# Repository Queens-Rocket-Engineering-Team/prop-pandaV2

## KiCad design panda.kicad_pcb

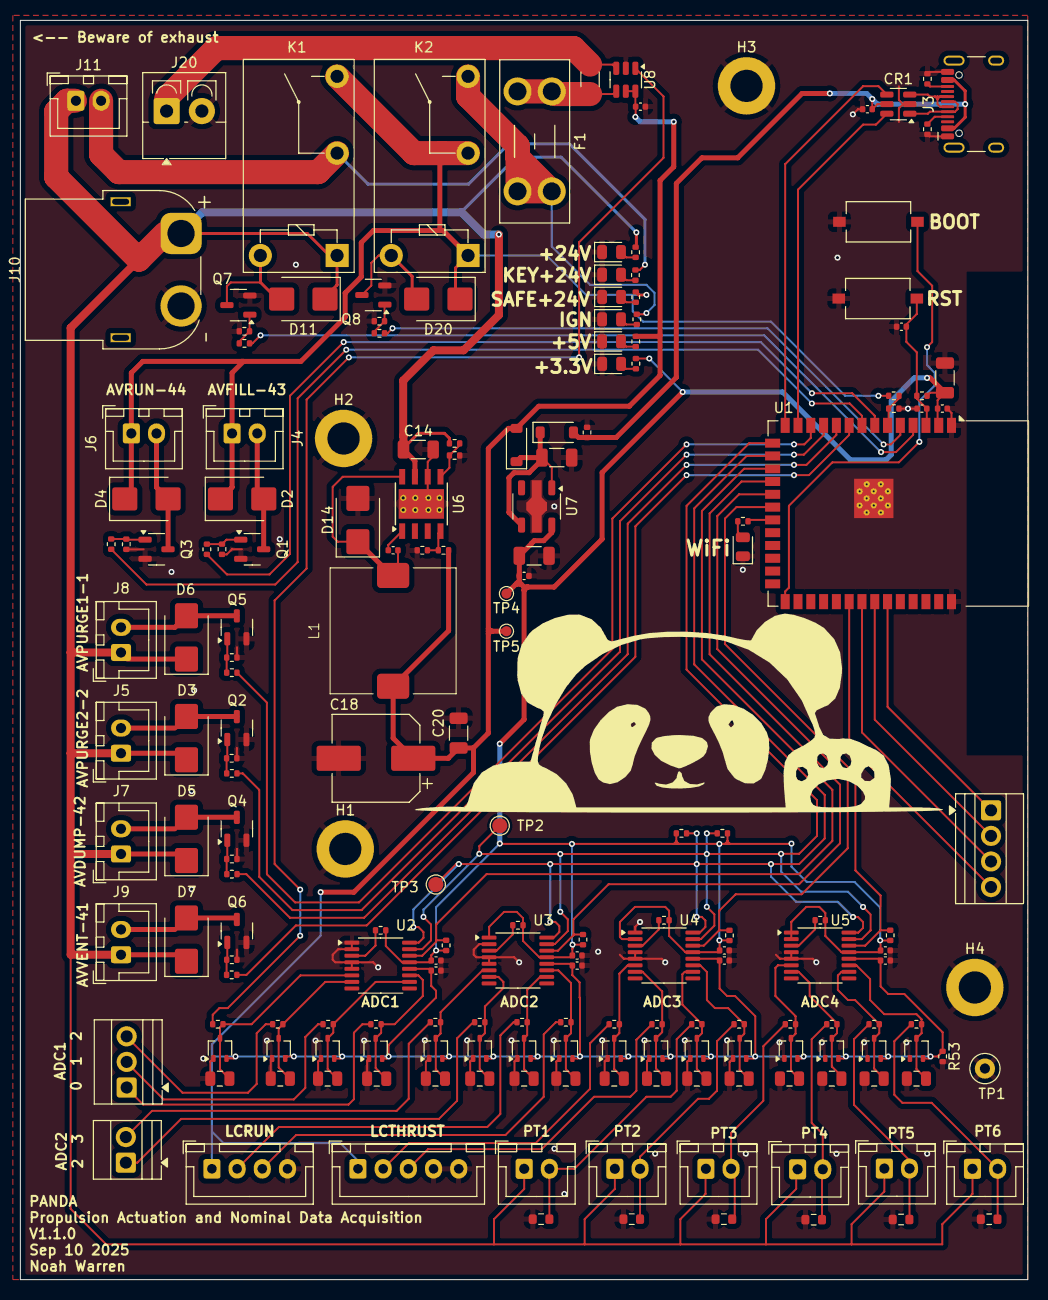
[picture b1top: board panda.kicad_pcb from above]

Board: 2 copper layers, 100.0 x 125.0 mm, 191 parts (0 on the bottom side), 102 nets.

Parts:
C1: 22uF; C_1206_3216Metric
C2, C3, C6, C7, C8, C9, C10, C11, C12, C13, C19, C21: 0.1μF; C_0402_1005Metric
C4: 1μF; C_0402_1005Metric
C5: 0.1uF; C_0402_1005Metric
C14, C15, C17, C20: 10uF; C_1206_3216Metric
C16: 10nF; C_0402_1005Metric
C18: 220uF; CP_Elec_8x10.5
C24, C25, C26, C27, C28, C29, C30, C31, C32, C33, C34, C35, C36, C37, C38, C39: 68nF; C_0805_2012Metric
CR1: USBLC6-2SC6; SOT-23-6
D1: LED-Y; LED_0805_2012Metric
D2, D3, D4, D5, D6, D7, D11, D14, D20: SK44BL; D_SMB
D8, D9, D10, D15, D16, D19: LED-G; LED_0805_2012Metric
D12, D13: 1N5819HW-7-F; D_SOD-123
D21, D22, D23, D24, D25, D26, D27, D28, D29, D30, D31, D32, D33, D34, D35, D36: BAT54SW; SOT-323_SC-70
F1: Fuse; Fuseholder_Blade_Mini_Keystone_3568
H1, H2, H3, H4: MountingHole_Pad; MountingHole_3.2mm_M3_ISO7380_Pad
J1: PIN10-13_Breakout; TerminalBlock_Xinya_XY308-2.54-4P_1x04_P2.54mm_Horizontal
J3: USB_C_Receptacle_USB2.0_16P; USB_C_Receptacle_HCTL_HC-TYPE-C-16P-01A
J4: Valve_1_PWR; JST_XH_B2B-XH-A_1x02_P2.50mm_Vertical
J5: Valve_4_PWR; JST_XH_B2B-XH-A_1x02_P2.50mm_Vertical
J6: Valve_2_PWR; JST_XH_B2B-XH-A_1x02_P2.50mm_Vertical
J7: Valve_5_PWR; JST_XH_B2B-XH-A_1x02_P2.50mm_Vertical
J8: Valve_3_PWR; JST_XH_B2B-XH-A_1x02_P2.50mm_Vertical
J9: Valve_6_PWR; JST_XH_B2B-XH-A_1x02_P2.50mm_Vertical
J10: XT60-M; AMASS_XT60PW-F_1x02_P7.20mm_Horizontal
J11: 24V_Lockout_Key_Switch; JST_XH_B2B-XH-A_1x02_P2.50mm_Vertical
J12: PT_1; JST_XH_B2B-XH-A_1x02_P2.50mm_Vertical
J13: PT_4; JST_XH_B2B-XH-A_1x02_P2.50mm_Vertical
J14: PT_2; JST_XH_B2B-XH-A_1x02_P2.50mm_Vertical
J15: PT_5; JST_XH_B2B-XH-A_1x02_P2.50mm_Vertical
J16: PT_3; JST_XH_B2B-XH-A_1x02_P2.50mm_Vertical
J17: PT_6; JST_XH_B2B-XH-A_1x02_P2.50mm_Vertical
J18: 4-Pin Load Cell; JST_XH_B4B-XH-A_1x04_P2.50mm_Vertical
J19: 5-Pin Load Cell; JST_XH_B5B-XH-A_1x05_P2.50mm_Vertical
J20: Ignitor Screw Terminal; TerminalBlock_4Ucon_1x02_P3.50mm_Vertical
J21: Screw_Terminal_01x03; TerminalBlock_Xinya_XY308-2.54-3P_1x03_P2.54mm_Horizontal
J22: Screw_Terminal_01x02; TerminalBlock_Xinya_XY308-2.54-2P_1x02_P2.54mm_Horizontal
K1, K2: G5Q-1A DC24; Relay_SPST_Omron-G5Q-1A
L1: 22uH 4A; L_12.5x12.5mm_SXNSMDRS1275
Q1, Q2, Q3, Q4, Q5, Q6, Q7, Q8: BSS138; SOT-23-3
R1, R21, R22, R25, R26, R31, R34, R38, R51, R53: 10k; R_0402_1005Metric
R2, R3, R6, R40: 1k; R_0402_1005Metric
R4, R5: 5.1k; R_0402_1005Metric
R7: 270k; R_0402_1005Metric
R8: 33k; R_0402_1005Metric
R9, R10, R13, R14, R17, R18, R35, R52: 100; R_0402_1005Metric
R11, R12, R15, R16, R19, R20, R30, R36: 100k; R_0402_1005Metric
R23, R24, R27, R28, R39: 3.3k; R_0402_1005Metric
R29, R32, R33, R50: 22k; R_0402_1005Metric
R37: 680; R_0402_1005Metric
R41, R42, R43, R44, R45, R46: 250R; R_0603_1608Metric
R49: 25m 1W; R_1206_3216Metric
R54, R55, R56, R57, R58, R59, R60, R61, R62, R63, R64, R65, R66, R67, R68, R69: 2.2k; R_0402_1005Metric
SW1, SW2: PTS636SM43SMTR LFS; SW_Tactile_SPST_NO_Straight_CK_PTS636Sx25SMTRLFS
TP1: TestPoint; TestPoint_Loop_D2.50mm_Drill1.0mm
TP2: SDA; TestPoint_Pad_D1.5mm
TP3: SCL; TestPoint_Pad_D1.5mm
TP4: TP_+3.3V; TestPoint_Pad_D1.0mm
TP5: TP_+5V; TestPoint_Pad_D1.0mm
U1: ESP32-S3-WROOM-1
U2, U3, U4, U5: ADS112C04; TSSOP-16_4.4x5mm_P0.65mm
U6: TPS5430DDA; TI_SO-PowerPAD-8_ThermalVias
U7: XC6220B331PR-G; SOT-89-5
U8: INA187A1; SOT-23-6

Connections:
5V_USB: C5.1, CR1.5, D13.2 (A), J3.A4 (VBUS), J3.A9 (VBUS), J3.B4 (VBUS), J3.B9 (VBUS), R36.2
24V_SAFE_DETECT: R7.2, R8.1, U1.6 (IO6)
+3.3V: C1.1, C3.1, C6.1, C7.1, C10.1, C11.1, C17.1, C19.1, R1.2, R2.1, R3.1, R21.1, R22.1, R23.1, R24.1, R25.1, R26.1, R27.1, R28.1, R37.2, TP4.1, U1.2 (3V3), U2.13 (DVDD), U3.1 (A0), U3.13 (DVDD), U4.2 (A1), U4.13 (DVDD), U5.1 (A0), U5.2 (A1), U5.13 (DVDD), U7.5 (VOUT)
+5V: C8.1, C9.1, C12.1, C13.1, C18.1, C20.1, C21.2, D12.2 (A), D21.2 (K), D22.2 (K), D23.2 (K), D24.2 (K), D25.2 (K), D26.2 (K), D27.2 (K), D28.2 (K), D29.2 (K), D30.2 (K), D31.2 (K), D32.2 (K), D33.2 (K), D34.2 (K), D35.2 (K), D36.2 (K), J18.1, J19.1, L1.2, R38.1, R40.2, R53.1, TP5.1, U2.12 (AVDD), U3.12 (AVDD), U4.12 (AVDD), U5.12 (AVDD), U8.5 (REF), U8.6 (V+)
+24V: C14.1, D3.1 (K), D5.1 (K), D6.1 (K), D7.1 (K), D11.1 (K), J5.1, J7.1, J8.1, J9.1, J10.1 (POS), J11.1, J12.1, J13.1, J14.1, J15.1, J16.1, J17.1, K1.1, R30.1, R32.2, U6.7 (VIN)
+24V_SAFE: D2.1 (K), D4.1 (K), D20.1 (K), J4.1, J6.1, K1.3, K2.1, K2.2, R7.1, R33.2
/Ignitor Control/IGNITOR_+VE: J20.1, R49.2, U8.3 (+)
/Ignitor Control/IGNITOR_CTL_FET: Q8.1 (G), R51.1, R52.1
/Ignitor Control/IGN_SUPPLY: F1.1, K2.3, R50.2
/Power Regulation/+24V_POST_LOCKOUT: J11.2, K1.2, R29.2
/Power Regulation/LOCKOUT_RLY_CTRL_FET: Q7.1 (G), R34.1, R35.1
/Power Regulation/VREG_EN: R30.2, R31.1, U6.5 (EN)
ADC1_AIN0: C25.1, D22.3 (COM), R57.2, U2.11 (AIN0)
ADC1_AIN1: C29.1, D26.3 (COM), R56.2, U2.10 (AIN1)
ADC1_AIN2: C28.1, D25.3 (COM), R55.2, U2.7 (AIN2)
ADC1_AIN3: C24.1, D21.3 (COM), R54.2, U2.6 (AIN3)
ADC2_AIN0: C27.1, D24.3 (COM), R61.2, U3.11 (AIN0)
ADC2_AIN1: C31.1, D28.3 (COM), R60.2, U3.10 (AIN1)
ADC2_AIN2: C30.1, D27.3 (COM), R59.2, U3.7 (AIN2)
ADC2_AIN3: C26.1, D23.3 (COM), R58.2, U3.6 (AIN3)
ADC3_AIN0: C33.1, D30.3 (COM), R65.2, U4.11 (AIN0)
ADC3_AIN1: C37.1, D34.3 (COM), R64.2, U4.10 (AIN1)
ADC3_AIN2: C36.1, D33.3 (COM), R63.2, U4.7 (AIN2)
ADC3_AIN3: C32.1, D29.3 (COM), R62.2, U4.6 (AIN3)
ADC4_AIN0: C35.1, D32.3 (COM), R69.2, U5.11 (AIN0)
ADC4_AIN1: C39.1, D36.3 (COM), R68.2, U5.10 (AIN1)
ADC4_AIN2: C38.1, D35.3 (COM), R67.2, U5.7 (AIN2)
ADC4_AIN3: C34.1, D31.3 (COM), R66.2, U5.6 (AIN3)
BOOT: SW2.1, U1.27 (IO0)
GND: C1.2, C2.2, C3.2, C4.2, C5.2, C6.2, C7.2, C8.2, C9.2, C10.2, C11.2, C12.2, C13.2, C14.2, C15.2, C17.2, C18.2, C19.2, C20.2, C21.1, C24.2, C25.2, C26.2, C27.2, C28.2, C29.2, C30.2, C31.2, C32.2, C33.2, C34.2, C35.2, C36.2, C37.2, C38.2, C39.2, CR1.2, D1.1 (K), D8.1 (K), D9.1 (K), D10.1 (K), D14.2 (A), D15.1 (K), D16.1 (K), D19.1 (K), D21.1 (A), D22.1 (A), D23.1 (A), D24.1 (A), D25.1 (A), D26.1 (A), D27.1 (A), D28.1 (A), D29.1 (A), D30.1 (A), D31.1 (A), D32.1 (A), D33.1 (A), D34.1 (A), D35.1 (A), D36.1 (A), H1.1, H2.1, H3.1, H4.1, J3.A1 (GND), J3.A12 (GND), J3.B1 (GND), J3.B12 (GND), J10.2 (NEG), J18.4, J19.4, J19.5, J20.2, Q1.2 (S), Q2.2 (S), Q3.2 (S), Q4.2 (S), Q5.2 (S), Q6.2 (S), Q7.2 (S), Q8.2 (S), R4.2, R5.2, R8.2, R11.2, R12.2, R15.2, R16.2, R19.2, R20.2, R31.2, R34.2, R36.1, R39.2, R41.2, R42.2, R43.2, R44.2, R45.2, R46.2, R51.2, R53.2, SW1.2, SW2.2, TP1.1, U1.1 (GND), U1.40 (GND), U1.41 (GND), U2.1 (A0), U2.2 (A1), U2.4 (DGND), U2.5 (AVSS), U3.2 (A1), U3.4 (DGND), U3.5 (AVSS), U4.1 (A0), U4.4 (DGND), U4.5 (AVSS), U5.4 (DGND), U5.5 (AVSS), U6.6 (GND), U6.9 (GNDPAD), U7.2 (GND), U8.2 (GND)
I2C_DRDY_ADC1: R23.2, U1.17 (IO9), U2.14 (DRDY)
I2C_DRDY_ADC2: R24.2, U1.18 (IO10), U3.14 (DRDY)
I2C_DRDY_ADC3: R28.2, U1.19 (IO11), U4.14 (DRDY)
I2C_DRDY_ADC4: R27.2, U1.20 (IO12), U5.14 (DRDY)
I2C_SCL: R3.2, TP3.1, U1.16 (IO46), U2.16 (SCL), U3.16 (SCL), U4.16 (SCL), U5.16 (SCL)
I2C_SDA: R2.2, TP2.1, U1.15 (IO3), U2.15 (SDA), U3.15 (SDA), U4.15 (SDA), U5.15 (SDA)
IGNITOR_CTL: R52.2, U1.5 (IO5)
IGN_Current_Measurement: R54.1, U8.1
LC_FILL_+: J18.2, R60.1
LC_FILL_-: J18.3, R61.1
LC_THRUST_+: J19.2, R62.1
LC_THRUST_-: J19.3, R63.1
MTCK: J1.4, U1.32 (IO39)
MTDI: J1.2, U1.34 (IO41)
MTDO: J1.3, U1.33 (IO40)
MTMS: J1.1, U1.35 (IO42)
unnamed: CR1.1, J3.A7 (D-), J3.B7 (D-)
unnamed: CR1.3, J3.A6 (D+), J3.B6 (D+)
unnamed: D1.2 (A), R6.1
unnamed: D8.2 (A), R29.1
unnamed: D9.2 (A), R32.1
unnamed: D10.2 (A), R33.1
unnamed: D11.2 (A), K1.5, Q7.3 (D)
unnamed: C15.1, D12.1 (K), D13.1 (K), U7.1 (CE), U7.4 (VIN)
unnamed: C16.2, D14.1 (K), L1.1, U6.8 (PH)
unnamed: D15.2 (A), R37.1
unnamed: D16.2 (A), R40.1
unnamed: D19.2 (A), R50.1
unnamed: D20.2 (A), K2.5, Q8.3 (D)
unnamed: J3.A5 (CC1), R4.1
unnamed: J3.B5 (CC2), R5.1
unnamed: J21.1, R57.1
unnamed: J21.2, R56.1
unnamed: J21.3, R55.1
unnamed: J22.1, R59.1
unnamed: J22.2, R58.1
unnamed: Q1.1 (G), R9.2, R11.1
unnamed: Q2.1 (G), R10.2, R12.1
unnamed: Q3.1 (G), R13.2, R15.1
unnamed: Q4.1 (G), R14.2, R16.1
unnamed: Q5.1 (G), R17.2, R19.1
unnamed: Q6.1 (G), R18.2, R20.1
unnamed: R21.2, U2.3 (RESET)
unnamed: R22.2, U3.3 (RESET)
unnamed: R25.2, U4.3 (RESET)
unnamed: R26.2, U5.3 (RESET)
unnamed: C16.1, U6.1 (BOOT)
unnamed: R38.2, R39.1, U6.4 (VSENSE)
unnamed: F1.2, R49.1, U8.4 (-)
PT_READING_1: J12.2, R41.1, R64.1
PT_READING_2: J14.2, R43.1, R65.1
PT_READING_3: J16.2, R45.1, R66.1
PT_READING_4: J13.2, R42.1, R67.1
PT_READING_5: J15.2, R44.1, R68.1
PT_READING_6: J17.2, R46.1, R69.1
RESET: C2.1, C4.1, R1.1, SW1.1, U1.3 (EN)
SAFE_24V_CTL: R35.2, U1.4 (IO4)
USB_N: CR1.6, U1.13 (USB_D-)
USB_P: CR1.4, U1.14 (USB_D+)
VALVE_1_CTL: R9.1, U1.7 (IO7)
VALVE_1_RET: D2.2 (A), J4.2, Q1.3 (D)
VALVE_2_CTL: R13.1, U1.8 (IO15)
VALVE_2_RET: D4.2 (A), J6.2, Q3.3 (D)
VALVE_3_CTL: R17.1, U1.12 (IO8)
VALVE_3_RET: D6.2 (A), J8.2, Q5.3 (D)
VALVE_4_CTL: R10.1, U1.11 (IO18)
VALVE_4_RET: D3.2 (A), J5.2, Q2.3 (D)
VALVE_5_CTL: R14.1, U1.10 (IO17)
VALVE_5_RET: D5.2 (A), J7.2, Q4.3 (D)
VALVE_6_CTL: R18.1, U1.9 (IO16)
VALVE_6_RET: D7.2 (A), J9.2, Q6.3 (D)
WIFI_IND: R6.2, U1.21 (IO13)

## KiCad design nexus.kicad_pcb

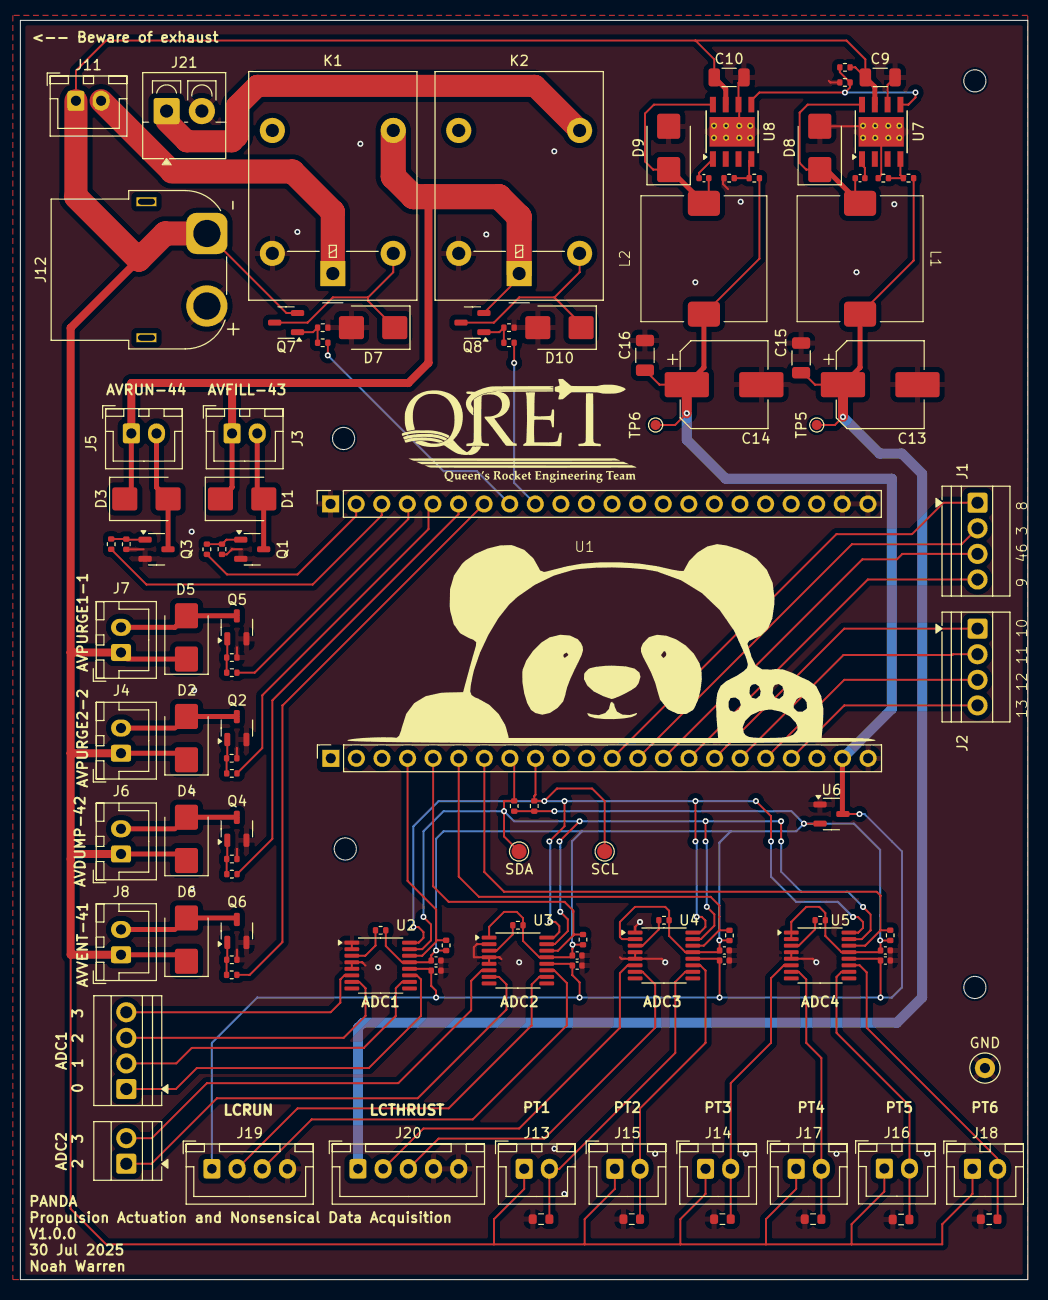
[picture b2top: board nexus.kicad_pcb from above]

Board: 2 copper layers, 100.0 x 125.0 mm, 110 parts (0 on the bottom side), 73 nets.

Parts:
C1, C2, C3, C4, C5, C6, C7, C8: 0.1μF; C_0402_1005Metric
C9, C10, C15, C16: 10uF; C_1206_3216Metric
C11, C12: 10nF; C_0402_1005Metric
C13, C14: 220uF; CP_Elec_8x10.5
D1, D2, D3, D4, D5, D6, D7, D8, D9, D10: SK44BL; D_SMB
GND: TestPoint_Loop_D2.50mm_Drill1.0mm
J1: PIN6-9_Breakout; TerminalBlock_Xinya_XY308-2.54-4P_1x04_P2.54mm_Horizontal
J2: PIN10-13_Breakout; TerminalBlock_Xinya_XY308-2.54-4P_1x04_P2.54mm_Horizontal
J3: Valve_1_PWR; JST_XH_B2B-XH-A_1x02_P2.50mm_Vertical
J4: Valve_4_PWR; JST_XH_B2B-XH-A_1x02_P2.50mm_Vertical
J5: Valve_2_PWR; JST_XH_B2B-XH-A_1x02_P2.50mm_Vertical
J6: Valve_5_PWR; JST_XH_B2B-XH-A_1x02_P2.50mm_Vertical
J7: Valve_3_PWR; JST_XH_B2B-XH-A_1x02_P2.50mm_Vertical
J8: Valve_6_PWR; JST_XH_B2B-XH-A_1x02_P2.50mm_Vertical
J9: Screw_Terminal_01x04; TerminalBlock_Xinya_XY308-2.54-4P_1x04_P2.54mm_Horizontal
J10: Screw_Terminal_01x02; TerminalBlock_Xinya_XY308-2.54-2P_1x02_P2.54mm_Horizontal
J11: 24V_Lockout_Key_Switch; JST_XH_B2B-XH-A_1x02_P2.50mm_Vertical
J12: XT60-M; AMASS_XT60PW-F_1x02_P7.20mm_Horizontal
J13: PT_1; JST_XH_B2B-XH-A_1x02_P2.50mm_Vertical
J14: PT_4; JST_XH_B2B-XH-A_1x02_P2.50mm_Vertical
J15: PT_2; JST_XH_B2B-XH-A_1x02_P2.50mm_Vertical
J16: PT_5; JST_XH_B2B-XH-A_1x02_P2.50mm_Vertical
J17: PT_3; JST_XH_B2B-XH-A_1x02_P2.50mm_Vertical
J18: PT_6; JST_XH_B2B-XH-A_1x02_P2.50mm_Vertical
J19: 4-Pin Load Cell; JST_XH_B4B-XH-A_1x04_P2.50mm_Vertical
J20: 5-Pin Load Cell; JST_XH_B5B-XH-A_1x05_P2.50mm_Vertical
J21: Ignitor Screw Terminal; TerminalBlock_4Ucon_1x02_P3.50mm_Vertical
K1, K2: G5LE-1; Relay_SPDT_Omron-G5LE-1
L1, L2: 22uH 4A; L_12.5x12.5mm_SXNSMDRS1275
Q1, Q2, Q3, Q4, Q5, Q6, Q7, Q8: BSS138; SOT-23-3
R1, R2: 1k; R_0402_1005Metric
R3, R4, R7, R8, R11, R12, R26, R38: 100; R_0402_1005Metric
R5, R6, R9, R10, R13, R14, R23: 100k; R_0402_1005Metric
R15, R16, R19, R20, R24, R25, R27, R29, R37: 10k; R_0402_1005Metric
R17, R18, R21, R22, R30: 3.3k; R_0402_1005Metric
R28: 1.4K; R_0402_1005Metric
R31, R32, R33, R34, R35, R36: 250; R_0603_1608Metric
SCL: SCL; TestPoint_Pad_D1.5mm
SDA: SDA; TestPoint_Pad_D1.5mm
TP5: TP_+10V; TestPoint_Pad_D1.0mm
TP6: TP_+5V; TestPoint_Pad_D1.0mm
U1: ESP32-S3; ESP32_Devkit_C1_Noah
U2, U3, U4, U5: ADS112C04; TSSOP-16_4.4x5mm_P0.65mm
U6: XC6206P332MR; SOT-23-3
U7, U8: TPS5430DDA; TI_SO-PowerPAD-8_ThermalVias

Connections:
+3.3V: C1.1, C2.1, C5.1, C6.1, R1.1, R2.1, R15.1, R16.1, R17.1, R18.1, R19.1, R20.1, R21.1, R22.1, U2.13 (DVDD), U3.1 (A0), U3.13 (DVDD), U4.2 (A1), U4.13 (DVDD), U5.1 (A0), U5.2 (A1), U5.13 (DVDD), U6.2 (VO)
+5V: C3.1, C4.1, C7.1, C8.1, C14.1, C16.1, J19.1, L2.2, R29.1, TP6.1, U1.5V (5VIN), U2.12 (AVDD), U3.12 (AVDD), U4.12 (AVDD), U5.12 (AVDD), U6.3 (VI)
+10V: C13.1, C15.1, J20.1, L1.2, R27.1, TP5.1
+24V: C9.1, C10.1, D2.1 (K), D4.1 (K), D5.1 (K), D6.1 (K), J4.1, J6.1, J7.1, J8.1, J11.1, J12.1 (POS), J13.1, J14.1, J15.1, J16.1, J17.1, J18.1, Q7.2 (S), R23.1, U7.7 (VIN), U8.7 (VIN)
+24V_SAFE: D1.1 (K), D3.1 (K), J3.1, J5.1, K1.3, K2.1, Q8.2 (S)
/ADC Circuitry/ADC1_AIN0: J9.1, U2.11 (AIN0)
/ADC Circuitry/ADC1_AIN1: J9.2, U2.10 (AIN1)
/ADC Circuitry/ADC1_AIN2: J9.3, U2.7 (AIN2)
/ADC Circuitry/ADC1_AIN3: J9.4, U2.6 (AIN3)
/ADC Circuitry/ADC2_AIN2: J10.1, U3.7 (AIN2)
/ADC Circuitry/ADC2_AIN3: J10.2, U3.6 (AIN3)
/ESP32 Breakout/PIN3_BREAKOUT: J1.2, U1.3 (GPIO3)
/ESP32 Breakout/PIN8_BREAKOUT: J1.1, U1.8 (GPIO8)
/ESP32 Breakout/PIN9_BREAKOUT: J1.4, U1.9 (GPIO9)
/ESP32 Breakout/PIN10_BREAKOUT: J2.1, U1.10 (GPIO10)
/ESP32 Breakout/PIN11_BREAKOUT: J2.2, U1.11 (GPIO11)
/ESP32 Breakout/PIN12_BREAKOUT: J2.3, U1.12 (GPIO12)
/ESP32 Breakout/PIN13_BREAKOUT: J2.4, U1.13 (GPIO13)
/ESP32 Breakout/PIN46_BREAKOUT: J1.3, U1.46 (GPIO46)
/Ignitor Control/IGNITOR_CTL_FET: Q8.1 (G), R37.1, R38.1
/Ignitor Control/IGNITOR_RLY_+VE: D10.1 (K), K2.2, Q8.3 (D)
/Ignitor Control/IGNITOR_SOURCE: J21.1, K2.3
/Power Regulation/+10V_REG_BOOT: C11.1, U7.1 (BOOT)
/Power Regulation/+10V_REG_PH: C11.2, D8.1 (K), L1.1, U7.8 (PH)
/Power Regulation/+10V_SENSE: R27.2, R28.1, U7.4 (VSENSE)
/Power Regulation/+24V_POST_LOCKOUT: J11.2, K1.1
/Power Regulation/LOCKOUT_RLY_+VE: D7.1 (K), K1.2, Q7.3 (D)
/Power Regulation/LOCKOUT_RLY_CTRL_FET: Q7.1 (G), R25.1, R26.1
/Power Regulation/VREG_EN: R23.2, R24.1, U7.5 (EN), U8.5 (EN)
GND: C1.2, C2.2, C3.2, C4.2, C5.2, C6.2, C7.2, C8.2, C9.2, C10.2, C13.2, C14.2, C15.2, C16.2, D7.2 (A), D8.2 (A), D9.2 (A), D10.2 (A), GND.1, J12.2 (NEG), J19.4, J20.4, J20.5, J21.2, K1.5, K2.5, Q1.2 (S), Q2.2 (S), Q3.2 (S), Q4.2 (S), Q5.2 (S), Q6.2 (S), R5.2, R6.2, R9.2, R10.2, R13.2, R14.2, R24.2, R25.2, R28.2, R30.2, R31.2, R32.2, R33.2, R34.2, R35.2, R36.2, R37.2, U1.GND1 (GND), U1.GND2 (GND), U1.GND3 (GND), U1.GND4 (GND), U2.1 (A0), U2.2 (A1), U2.4 (DGND), U2.5 (AVSS), U3.2 (A1), U3.4 (DGND), U3.5 (AVSS), U4.1 (A0), U4.4 (DGND), U4.5 (AVSS), U5.4 (DGND), U5.5 (AVSS), U6.1 (GND), U7.6 (GND), U7.9 (GNDPAD), U8.6 (GND), U8.9 (GNDPAD)
I2C_DRDY_ADC1: R17.2, U1.4 (GPIO4), U2.14 (DRDY)
I2C_DRDY_ADC2: R18.2, U1.5 (GPIO5), U3.14 (DRDY)
I2C_DRDY_ADC3: R22.2, U1.6 (GPIO6), U4.14 (DRDY)
I2C_DRDY_ADC4: R21.2, U1.7 (GPIO7), U5.14 (DRDY)
I2C_SCL: R2.2, SCL.1, U1.16 (GPIO16/XTAL_32K_N), U2.16 (SCL), U3.16 (SCL), U4.16 (SCL), U5.16 (SCL)
I2C_SDA: R1.2, SDA.1, U1.15 (GPIO15/XTAL_32K_P), U2.15 (SDA), U3.15 (SDA), U4.15 (SDA), U5.15 (SDA)
IGNITOR_CTL: R38.2, U1.39 (GPIO39)
LC_FILL_+: J19.2, U3.10 (AIN1)
LC_FILL_-: J19.3, U3.11 (AIN0)
LC_THRUST_+: J20.2, U4.6 (AIN3)
LC_THRUST_-: J20.3, U4.7 (AIN2)
unnamed: C12.2, D9.1 (K), L2.1, U8.8 (PH)
unnamed: Q1.1 (G), R3.2, R5.1
unnamed: Q2.1 (G), R4.2, R6.1
unnamed: Q3.1 (G), R7.2, R9.1
unnamed: Q4.1 (G), R8.2, R10.1
unnamed: Q5.1 (G), R11.2, R13.1
unnamed: Q6.1 (G), R12.2, R14.1
unnamed: R15.2, U2.3 (RESET)
unnamed: R16.2, U3.3 (RESET)
unnamed: R19.2, U4.3 (RESET)
unnamed: R20.2, U5.3 (RESET)
unnamed: C12.1, U8.1 (BOOT)
unnamed: R29.2, R30.1, U8.4 (VSENSE)
PT_READING_1: J13.2, R31.1, U4.10 (AIN1)
PT_READING_2: J15.2, R33.1, U4.11 (AIN0)
PT_READING_3: J17.2, R35.1, U5.7 (AIN2)
PT_READING_4: J14.2, R32.1, U5.6 (AIN3)
PT_READING_5: J16.2, R34.1, U5.10 (AIN1)
PT_READING_6: J18.2, R36.1, U5.11 (AIN0)
SAFE_24V_CTL: R26.2, U1.40 (GPIO40)
VALVE_1_CTL: R3.1, U1.43 (GPIO43)
VALVE_1_RET: D1.2 (A), J3.2, Q1.3 (D)
VALVE_2_CTL: R7.1, U1.44 (GPIO44)
VALVE_2_RET: D3.2 (A), J5.2, Q3.3 (D)
VALVE_3_CTL: R11.1, U1.1 (GPIO1)
VALVE_3_RET: D5.2 (A), J7.2, Q5.3 (D)
VALVE_4_CTL: R4.1, U1.2 (GPIO2)
VALVE_4_RET: D2.2 (A), J4.2, Q2.3 (D)
VALVE_5_CTL: R8.1, U1.42 (GPIO42)
VALVE_5_RET: D4.2 (A), J6.2, Q4.3 (D)
VALVE_6_CTL: R12.1, U1.41 (GPIO41)
VALVE_6_RET: D6.2 (A), J8.2, Q6.3 (D)

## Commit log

2025-07-27 Add power regulation schematic
2025-07-27 Add valve control
2025-07-27 Add SAFE +24V
2025-07-27 Add .gitignore
2025-07-28 Add load cell inputs
2025-07-28 v0.1 sch. Add devkit c1 footprint
2025-07-28 Add all footprints
2025-07-29 Almost done routing
2025-07-29 Fix J5
2025-07-30 routing broken
2025-07-30 Fix connector references
2025-07-30 Route buck converters
2025-07-30 Route first solenoid
2025-07-30 Route All solenoids
2025-07-30 Route I2C lines and ADC communications
2025-07-30 Route power to sensors
2025-07-30 Satisfy DRC
2025-07-30 Add Mounting Holes
2025-07-30 Add silk screening
2025-07-30 Update silk screening
2025-07-30 PANDA Rebrand
2025-07-30 Fix inductor layout
2025-07-30 Fix silk screening
2025-07-30 Complete panda rename
2025-07-31 PCB v1.0.0 Ordered
2025-08-27 Switch relay driving FETs to low side. Relays changed to SPST instead of SPDT
2025-08-27 Actually fix XT60 silkscreen and placement
2025-08-27 Swap PT3 and PT4 connectors so they are connected to teh proper pins
2025-08-27 Actually fix PT3 and PT4 mapping
2025-08-27 Update thrust LC to take +5V. Remove +10V rail
2025-09-07 Add signal conditioning. Change screw hole footprint
2025-09-07 Update +5V rail wiring for adcs and signal conditioning
2025-09-10 Add current sensing and fuse mount for IGN
2025-09-10 Add indicator LEDs and digital +24VSafe detection line
2025-09-10 Update version numbers
2025-09-10 Create V1.1.0 production files
2025-10-07 Completed necessary ESP32 wiring + new 3.3V LDO. GPIO pins not yet connected
2025-10-09 connected to GPIO pins
2025-10-13 added 24V lockout key LED indicator
2025-10-16 added ignitor current sensor overvoltage protection
2025-10-17 pcb first draft, changed esp32 pin connections
2025-10-18 replaced ignitor current sensor with INA187A3 for higher voltage tolerance
2025-10-18 fixed 5v rail connection for signal conditioning
2025-11-02 changed CSA to INA187A1 from INA187A3 for availability
